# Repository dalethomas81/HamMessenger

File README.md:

> **⚠️ This repository is archived and no longer maintained.**  
> The code is left available for reference. No further updates, issues, or pull requests will be accepted.
> Please see [Meshtastic](https://meshtastic.org) or [Meshcore](https://meshcore.io) as superior alternatives. 

# HamMessenger # 

Hands on article about HamMessenger in IEEE Spectrum magazine [here](https://spectrum.ieee.org/ham-radio-text-hacking)  
Arduino blog post on HamMessenger [here](https://blog.arduino.cc/2021/07/27/send-text-messages-over-ham-radio-with-the-hammessenger/?queryID=undefined)  
Hackaday blog post on HamMessenger [here](https://hackaday.com/blog/?s=hammessenger)  

HamMessenger is a portable, battery powered device that runs on a microcontroller and interfaces with an inexpensive ham radio to send and receive text messages and provide position updates using the [APRS](http://www.aprs.org/doc/APRS101.PDF) protocol. Messages and position updates sent via HamMessenger can be viewed on sites such as [aprs.fi](https://aprs.fi). HamMessenger messages are NOT encrypted!  

HamMessenger is intended to be used by licensed ham radio operators. For more information you can check out the [ARRL](http://www.arrl.org/what-is-ham-radio) website.  

The goal of the HamMessenger project is to create a device that uses ham radio as a medium for sending and receiving text messages. HamMessenger exists also to promote amateur radio, electronics, and programming. The project is currently in a beta prototyping stage but does function quite well. 

At the core of the the project is the [MicroAPRS](https://github.com/markqvist/MicroAPRS) modem created by [markqvist](https://github.com/markqvist). The primary controller is an Arduino Mega 2560 with the MicroAPRS Modem running on an Arduino Pro Mini. HamMessenger includes GPS functionality supplied by a Neo-6M GPS radio. For peripherals, an M5Stack CardKB keyboard is used for input and an SSD1106 Oled display for output.  

I will add some videos and pictures of the device in action asap. Please feel free to contribute to the project. I am very busy outside of this project so any help is greatly appreciated :)  

<table>
  <tr>
    <td align="center">
      <br/>
      <sub>MacOS Log Screen</sub>
    </td>
    <td align="center">
      <br/>
      <sub>MacOS Map Screen</sub>
    </td>
  </tr>
</table>

<table>
  <tr>
    <td align="center">
      <br/>
      <sub>MacOS Message Screen</sub>
    </td>
    <td align="center">
      <br/>
      <sub>MacOS Commands Example</sub>
    </td>
  </tr>
</table>

<table>
  <tr>
    <td align="center">
      <br/>
      <sub>Full Enclosure</sub>
    </td>
    <td align="center">
      <br/>
      <sub>Component Layout</sub>
    </td>
    <td align="center">
      <br/>
      <sub>CAD Isometric</sub>
    </td>
  </tr>
</table>

## Operation ##

Full instructions on how to operate HamMessenger will go here. For now, just a couple notes :)  

HamMessenger will beacon your location and comment according to the 'Beacon' settings in `APRS` Settings.  
- `Beacon Distance` is the distance in miles that will trigger a beacon.  
- `Beacon Idle Time` is the time in milliseconds that the station must be in the same location after having moved from the last beacon location before a beacon will be sent.
- `Position Tolerance` under `GPS` settings is the +/- value that will trigger a location update.  

To send a direct message to a station, select `Messages` on the `HOME` screen and press `Enter` on the keyboard. This will open the `NEW MESSAGE` screen.  
- `Message Text` is the message that will be sent.  
- `Recipient Callsign` is the callsign of the station that will recieve the message. Example 'NOCALL-ID'  
- `Recipient SSID` is the ID of the station that will recieve the message. Example 'NOCALL-ID'  

Screen navigation information can be found [here](https://github.com/dalethomas81/HamMessenger/blob/master/Documentation/Operating%20Instructions/Screen%20Navigation.md).  

Radio setup instructions can be found [here](https://github.com/dalethomas81/HamMessenger/blob/master/Documentation/Operating%20Instructions/Radio%20Setup.md).

Serial interface information can be found [here](https://github.com/dalethomas81/HamMessenger/blob/master/Documentation/Operating%20Instructions/Serial%20Interface.md).

## TODO ##

hardware:
- improve enclosure design  

software:
- add ability to program the radio once connected for 'plug-n-play' experience (is this possible?)  
- add feature to be selective about message acknowledgments. currently any acknowlegment (from a second conversation) will reset the messaging sequencer.  

## Libraries ##

Here are links to the non-standard libraries that I am using for this project. All other libraries are standard and can be installed using the library manager built into the Arduino IDE.  
- https://github.com/wonho-maker/Adafruit_SH1106  
- https://github.com/mikalhart/TinyGPSPlus  
- https://github.com/adafruit/Adafruit-GFX-Library  
- https://github.com/Xander-Electronics/Base64  

## Compilation ##

The easiest way to compile HamMessenger is to use the Ardunio IDE. After all libraries are installed you can use the Verify button to compile or the Upload button to compile and write the binary to the main controller M1. 

The Arduino source code for HamMessenger can be found [here](/Source/HamMessenger).

The modem controller does not need to be compiled as the binary files are already made available [here](https://github.com/markqvist/MicroAPRS/tree/master/precompiled).  

You can use AVRDude to write the binary to the modem controller. Instructions on how to do that will be coming soon. In the meantime, if you already know how to install and use AVRDude then feel free to make use of the [batch](/Source/MicroAPRS%20Firmware%20Installer) file I created and an [FTDI](https://www.amazon.com/gp/product/B00DDF8TV6/ref=ox_sc_act_title_4?smid=A2SXV8GJXX3WPH&psc=1) serial cable to write to the modem.

## Parts ##

Find BOM information on parts [here](/Documentation/Parts/BOMs)  
Find Drawing information on parts [here](/Documentation/Parts/Drawings)  
Find Vendor information on parts [here](/Documentation/Parts/Vendors)  

### Part Specs ###

Arduino:  
https://gallery.autodesk.com/fusion360/projects/arduino-mega-2560-r3  

Keyboard:  
https://github.com/m5stack/M5-ProductExampleCodes/tree/master/Unit/CARDKB  

OLED Display:    
https://grabcad.com/library/0-96-oled-display-4-pin-1  
https://grabcad.com/library/ecran-oled-1-3-1

Modem:  
https://github.com/markqvist/MicroAPRS  
https://github.com/markqvist/MicroAPRS/blob/master/precompiled/microaprs-5v-ss-latest.hex  
https://github.com/markqvist/MicroAPRS/blob/master/documentation/Hardware%20Schematic.pdf  
https://unsigned.io/shop  
https://unsigned.io/product/micromodem-r23b  

GPS:    
https://grabcad.com/library/gps-module-ublox_neo6mv2-1  
https://grabcad.com/library/ecran-oled-1-3-1  

Grove Connector:  
https://grabcad.com/library/grove-connectors-stand-and-flat-male-plugs-1/details?folder_id=2820551  

Battery:  
Panasonic 18650 - don't have a link but you can get them on eBay or Amazon  

## Updates ##

### 31-MAY-2025: Major updates!

I have made some major updates to the board (RF filtering for the PTT), to the enclosure, and to the firmware (many improvements to the display including a dedicated "New Message" display). Additionally, I have created a companion GUI app that you can use to connect HamMessenger to your PC.  

I have ordered parts to begin building 3 new HamMessengers and will begin building them next week. The purpose is to create some instructional videos and documentation to help support anyone that wants to build one themselves. I also plan to donate these builds to my local Ham club.  

There is now a new [Build Instructions](/Documentation/Build%20Instructions/) folder that I will use to put the tutorial references and documentation.  

### 08-SEP-2021: Troubleshooting freezing

There is an issue where during transmit the unit will freeze or restart. I did some experimenting and found out that its the cable that connects to the radio. It is not shielded at all. I thought the small ferrites would be enough to combat this but obviously not. I did some experimenting and found that if I use larger ferrites and wrap them once that the issue goes away. [Here](/Media/Install/large-ferrites.jpeg/) is a picture of the installation. I will now look at sourcing a shielded cable for this application.

### 05-SEP-2021: First version of the enclosure

So I started learning 3D modeling so that I can create an enclosure for HamMessenger. Its been a bit of a learning curve but I'm getting the hang of it. I decided that for the first iteration I would go with an open unibody frame. I chose this style for the first version because it is easy and I'd like to have something working while I learn more about 3D modeling.

You can find the Fusion 360 archive file and the stl [here](/Documentation/CAD/Fusion-360/). It needs to be printed on its side like [this](/Media/Unibody-Frame-v1/cura.png/) to minimize the amount of support needed during printing. I used 0.2mm layers with 20% infill as well as 5% support infill. The print took about 6.5 hours.

A few pics:  
[Front](/Media/Unibody-Frame-v1/front.jpeg/)  
[Side](/Media/Unibody-Frame-v1/side.jpeg/)  
[Back](/Media/Unibody-Frame-v1/back.jpeg/)  

### 14-AUG-2021: Rev v1.1 has arrived and it works!

Ok, great news. Revision v1.1 of the HamMessenger board came in from PCBWay and they are great. I built 2 units and was able to encode and decode messages well. I will add some more information later but [here](/Media/Board-v1.1/) is a few pictures for now.

### 24-JUL-2021: Rev v1.1 is being fabbed!!

I was able to work through all of the issues with the first version. I placed an order with jlcpcb this time (osh park was great but too expensive). I ordered 20 boards this time and if they work well I will give some away.  

I'll update later with how I resolved the issues. For now, going to have a beer :)

### 22-JUL-2021: Put together some information on the board for your review.

[Here](/Media/Board-v1/analysis.md) is an in-depth analysis of the problems with version 1.0 of the board. Also, does any body know how to add correct shielding for the board? I am having issues with the Arduino locking up on transmit sometimes.

### 21-JUL-2021: Made revisons to the board resolving and improving the following:

1. add ground to SD card
2. add OE connection to line leveler
3. reverse I2C connections
4. change GPS I/O to correct serial
5. purchase correct GPS (added new link in BOM)
6. move SD card away from USB.
7. move keyboard grove to bottom of board and out of way
8. move 4 pin terminal for cable such that it is out of the way of larger OLED
9. ground plane improvements.  

still left to do:

1. board does not receive (soldering issues?)  
2. board some times locks up during transmit (ground plane issues?)  

### 20-JUL-2021: Bad news on the boards :( Lots of problems. I will begin immediately working on a revision. Here is a list of the issues:

1. SD Card missing ground
2. Line leveler missing OE connection.
3. I2C connections are reversed.
4. GPS is pointing to wrong serial ports (can fix with code but might as well make it right).
5. GPS pins do not match board. (worked around this by shifting pins)
6. Cannot not receive (don't know why at this point).
7. SD card hits Arduino USB. Will move it and the Grove connector to make room.
8. Arduino periodically locks up. Seemingly due to RF? Had this issue with prototype board but fixed it with ferrites.

### 18-JUL-2021: The printed circuit boards from OSH will be arriving tomorrow! I have added all of the parts needed to build HamMessenger [here](/Documentation/Parts/BOMs).

04-JUL-2021: Version 1 of the pcb for HamMessenger has be sent for fabrication. The estimated delivery date is the 22nd of July. In the meantime I will be ordering the components to populate the board. As I do that I will make sure to get the links for the components and add them to the BOM in the Eagle folder.

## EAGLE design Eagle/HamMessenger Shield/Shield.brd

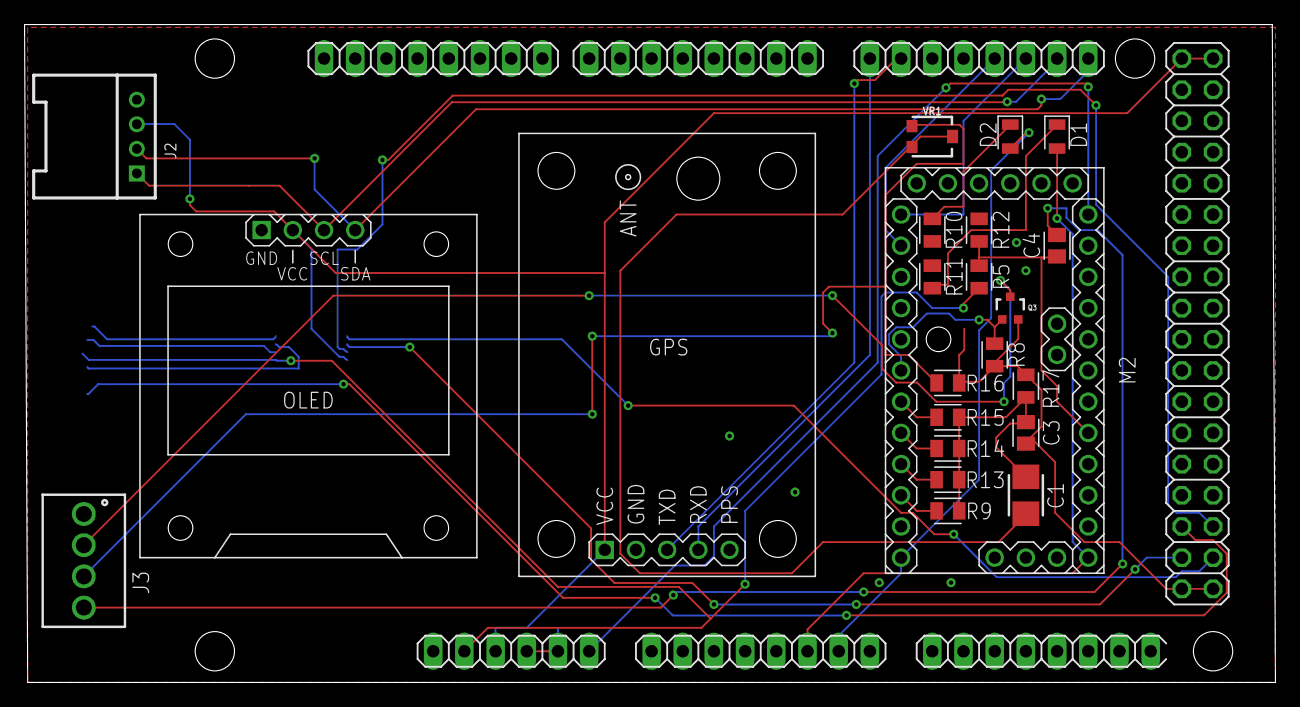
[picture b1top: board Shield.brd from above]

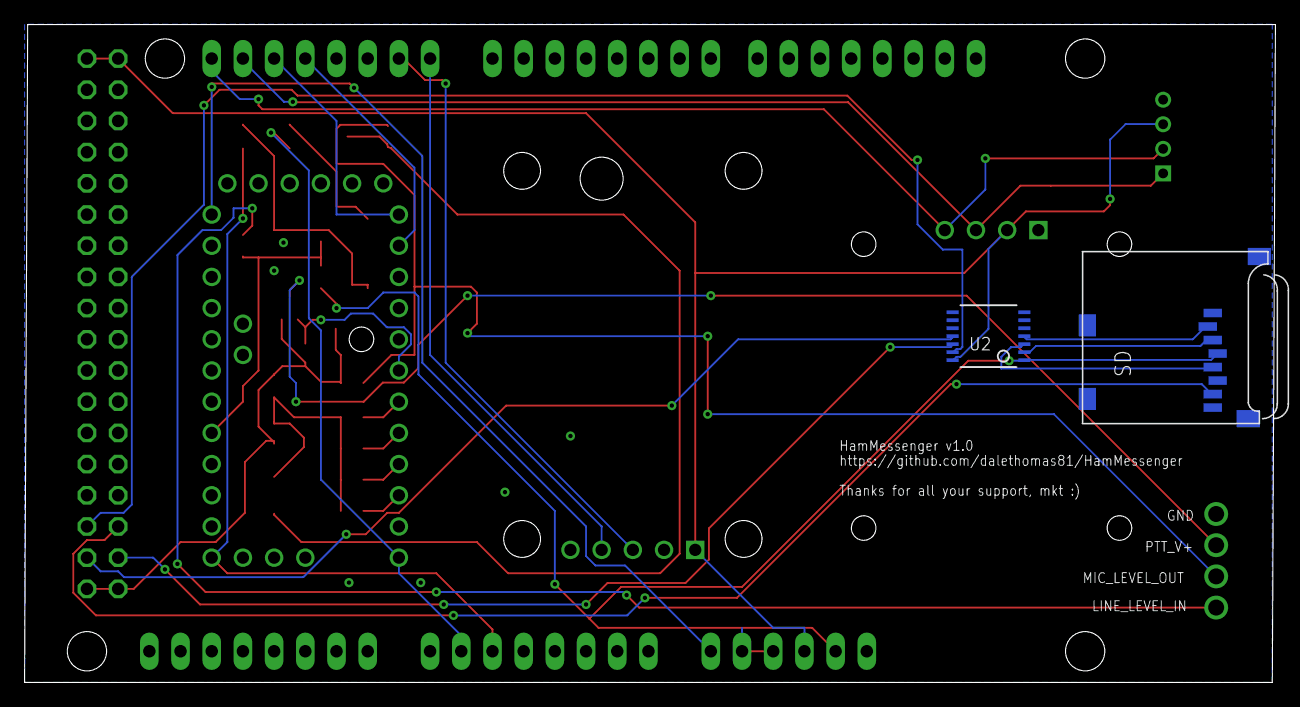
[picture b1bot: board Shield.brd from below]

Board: 2 copper layers, 101.9 x 53.6 mm, 26 parts (2 on the bottom side), 32 nets.

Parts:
C1: 4.7uf; CT3528
C3: 100nf; CAPC2012X110
C4: 1uf; CAPC2012X110
D1: LED_GREEN; LEDC2012X105N_RND-R
D2: LED_RED; LEDC2012X105N_RND-R
GPS: GPS-RECEIVER-NEO6M
J2: KEYBOARD GROVE; HW4-2.0-90D
J3: 691210910004
M1: MEGA_ARDUINO
M2: ARDUINO-PRO-MINI-3.3V; ARDUINO-PRO-MINI
OLED: DISPLAY-OLED-128X64-I2C
Q3: MOSFET-NCHANNEL2N7002PW; SOT323
R5, R12: 100k; RESC2012X65
R8: 10k; RESC2012X65
R9, R11, R16: 1k; RESC2012X65
R10: 270k; RESC2012X65
R13: 2k2; RESC2012X65
R14: 3k9; RESC2012X65
R15: 8k2; RESC2012X65
R17: 270; RESC2012X65
SD: MICROSD
U2: TSSOP14
VR1: 100k; TRIMPOT-SMD-3MM-CLOSED

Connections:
+3V3: M1.2, R5.2, SD.4, U2.1
+5V: GPS.1, J2.3, M1.3, M1.47, M1.48, OLED.2, U2.14
A0: C4.1, M2.J6.8, R5.1, R12.2
D3: M2.J7.7, Q3.1, R8.2
D4: M2.J7.6, R15.2
D5: M2.J7.5, R14.2
D6: M2.J7.4, R13.2
D7: M2.J7.3, R9.2
D9: D2.A, M1.13, M2.J7.1
D10: D1.A, M1.12, M2.J6.12
GND: C3.2, GPS.2, J2.4, J3.1, M1.4, M1.5, M1.45, M1.81, M1.82, M2.J6.2, M2.J7.9, OLED.1, Q3.2, R8.1, R10.1, R11.1, R12.1, R16.1, R17.1, SD.MT1, SD.MT2, U2.7
LINE_LEVEL_IN: C4.2, J3.4
LINE_LEVEL_OUT: C1.+, VR1.2, VR1.3
MIC_LEVEL_OUT: J3.3, R16.2, VR1.1
MISO: M1.77, SD.7
MOSI: M1.78, U2.13
unnamed: SD.3, U2.2
unnamed: C1.-, C3.1, R9.1, R13.1, R14.1, R15.1, R17.2
unnamed: D2.C, R10.2
unnamed: D1.C, R11.2
unnamed: SD.5, U2.3
unnamed: SD.2, U2.4
PTT_V+: J3.2, Q3.3
RX_GPS: GPS.3, M1.29
RX_MODEM: M1.25, M2.J7.12
SCK: M1.79, U2.12
SCL: J2.1, M1.24, OLED.3
SDA: J2.2, M1.23, OLED.4
SS: M1.80, U2.11
TX_GPS: GPS.4, M1.30
TX_MODEM: M1.26, M2.J7.11
VCC: M1.6, M2.J6.1, M2.J6.4

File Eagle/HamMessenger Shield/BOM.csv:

"Part";"Value";"Device";"Package";"Description";"CATEGORY";"COLOR";"URL";"PART-NUMBER";"PINS";"PITCH";"PROD_ID";"TYPE";"VALUE";"WORKING-VOLTAGE-UL";
"C1";"4.7uf";"CPOL-USCT3528";"CT3528";"POLARIZED CAPACITOR, American symbol";"Capacitor";;;"T591B475M035ATE200";;;;;;;
"C3";"100nf";"C_CHIP-0805(2012-METRIC)";"CAPC2012X110";"Capacitor - Generic";"Capacitor";;;"C0805C104J4RACTU";;;;;;;
"C4";"1uf";"C_CHIP-0805(2012-METRIC)";"CAPC2012X110";"Capacitor - Generic";"Capacitor";;;"C0805C105J4RECTU";;;;;;;
"D1";"Green";"CHIP-ROUND-R_0805";"LEDC2012X105N_RND-R";"LED - Generic";"LED";"RED";;"SM0805UGC";;;;"ROUND_TOP";"LED_RED";;
"D2";"Red";"CHIP-ROUND-R_0805";"LEDC2012X105N_RND-R";"LED - Generic";"LED";"RED";;"SM0805URC";;;;"ROUND_TOP";"LED_RED";;
"IC1";;"MEGAARDUINO_1";"MEGA_ARDUINO";"The Arduino Mega is a microcontroller board based on the ATmega2560";;;"https://www.amazon.com/ELEGOO-ATmega2560-ATMEGA16U2-Projects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";;;;;;;;
"J2";;"GROVE-CONNECTOR-DIP-90D(4P-2.0)";"HW4-2.0-90D";;;;"https://www.seeedstudio.com/Grove-Universal-4-pin-connector-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";"110990037";;;;;"4P-2.0-90D";;
"J3";;"691210910004";"691210910004";"WR-TBL Serie 2109 - 2.54 mm Horiz. Entry";;;"https://www.we-online.com/catalog/datasheet/691210910004.pdf";"282834-4";" 4 ";"2.54mm";;"Horizontal";;"150V (AC)";
"M1";;"ARDUINO-PRO-MINI-3.3V";"ARDUINO-PRO-MINI";"The Arduino Mega is a microcontroller board based on the ATmega328P";;;"https://www.amazon.com/HiLetgo-Atmega328P-Replace-ATmega128-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";;;;;;;;
"Q3";;"MOSFET-NCHANNEL2N7002PW";"SOT323";"Common NMOSFET Parts";;;;;;;"TRANS-11151";;;;
"R5";"100k";"R_CHIP-0805(2012-METRIC)";"RESC2012X65";"Resistor Fixed - Generic";"Resistor";;;;;;;;;;
"R8";"10k";"R_CHIP-0805(2012-METRIC)";"RESC2012X65";"Resistor Fixed - Generic";"Resistor";;;;;;;;;;
"R9";"1k";"R_CHIP-0805(2012-METRIC)";"RESC2012X65";"Resistor Fixed - Generic";"Resistor";;;;;;;;;;
"R10";"270k";"R_CHIP-0805(2012-METRIC)";"RESC2012X65";"Resistor Fixed - Generic";"Resistor";;;;;;;;;;
"R11";"1k";"R_CHIP-0805(2012-METRIC)";"RESC2012X65";"Resistor Fixed - Generic";"Resistor";;;;;;;;;;
"R12";"100k";"R_CHIP-0805(2012-METRIC)";"RESC2012X65";"Resistor Fixed - Generic";"Resistor";;;;;;;;;;
"R13";"2k2";"R_CHIP-0805(2012-METRIC)";"RESC2012X65";"Resistor Fixed - Generic";"Resistor";;;;;;;;;;
"R14";"3k9";"R_CHIP-0805(2012-METRIC)";"RESC2012X65";"Resistor Fixed - Generic";"Resistor";;;;;;;;;;
"R15";"8k2";"R_CHIP-0805(2012-METRIC)";"RESC2012X65";"Resistor Fixed - Generic";"Resistor";;;;;;;;;;
"R16";"1k";"R_CHIP-0805(2012-METRIC)";"RESC2012X65";"Resistor Fixed - Generic";"Resistor";;;;;;;;;;
"R17";"270";"R_CHIP-0805(2012-METRIC)";"RESC2012X65";"Resistor Fixed - Generic";"Resistor";;;;;;;;;;
"GPS";;"GPS-RECEIVER-NEO6M";"GPS-RECEIVER-NEO6M";"GPS Receiver Module based on NEO-6 device";;;;;;;;;;;
"OLED";;"DISPLAY-OLED-128X64-I2C";"DISPLAY-OLED-128X64-I2C";"128x64 Dot Matrix OLED Module based on SSD1306 chip";;;;;;;;;;;
"SD";;"MICROSD";"MICROSD";"Micro-SD / Transflash card holder with SPI pinout";;;;;;;;;;;
"U2";;"TXB0104PWR";"TSSOP14";"4-Bit Bi-Directional Level Shifter";;;;;;;;;;;
"VR1";"100k";"TRIMPOT-SMD-3MM-CLOSED-1/8W-20%";"TRIMPOT-SMD-3MM-CLOSED";"Trimming Potentiometer (Trimpot)";;;;;;;"RES-09285";;"10k";;

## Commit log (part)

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2021-06-26 init
2021-06-26 add media
2021-06-27 add serial commands table
2021-06-27 update readme. add print and save to serial
2021-06-27 Convert settings array references to use macros
2021-06-27 Improve readme serial commands
2021-06-27 add modem command to printout
2021-06-27 improve serial commands in readme
2021-06-27 Add raw packet info
2021-06-27 clarify what HamMessenger is
2021-06-27 add uint edit to aprs settings
2021-06-27 esc button cancels edit. enter button confirms.
2021-06-27 use temp variable for strings
2021-06-27 add remaining settings to temp variables
2021-06-27 remove reference to buttons
2021-06-27 add #defines for keyboard keys
2021-06-27 add macros for keyboard keys
2021-06-27 add edit capability to settings_gps
2021-06-27 add edit capablities to settings_display
2021-06-27 optimize settings screen
2021-06-27 fix issue where float doesnt copy to temp var
2021-06-28 fix issue where float val does not negate
2021-06-28 general code cleanup. update readme.
2021-06-28 refactor temp var handling into functions
2021-06-28 refactor printing value stored in mem to function
2021-06-28 general refactoring
2021-06-29 Begin work on PCB. Add schematic (WIP)
2021-06-30 Continue work on PCB. Update schematic.
2021-07-01 Fix settings arent accepted via command prompt
2021-07-01 Add quick way to send messages. Update readme.
2021-07-01 Fix issue with dynamic number of items in settings
2021-07-01 added sequencer for sending messages
2021-07-02 init test writing and reading sd card
2021-07-02 remove unneeded reference to SD library
2021-07-02 general code clean up and variable optimizing
2021-07-02 code clean up
2021-07-02 General refactoring. Update readme.
2021-07-02 add feature to retry messages if not acknowledged
2021-07-03 add retry count and interval to settings.
2021-07-03 add display timeout - dim then turn off
2021-07-03 key press only register when screen awake
2021-07-03 variable names cleanup
2021-07-03 fix issue with gps tolerance
2021-07-03 update readme and settings names.
2021-07-03 add references
2021-07-03 add dxf for arduino mega 2560
2021-07-03 add notes. start ui documentation.
2021-07-03 improve message and feed scrolling.
2021-07-04 Add screenshots. Continue work on UI map.
2021-07-04 test relative path image
2021-07-04 check
2021-07-04 Update UI
2021-07-04 add screenshots
2021-07-04 Formatting
2021-07-04 Net re-routing
2021-07-04 PCB Updates
2021-07-04 Add ground plane
2021-07-04 add SD card. rerouting.
2021-07-05 Update readme. Add isometic view.
2021-07-05 Update readme. Relative photos.
2021-07-05 add grove connector
2021-07-05 Add text to silkscreen
2021-07-05 Change pins grove keyboard connector.
2021-07-05 Last minute tweeks before sending to fab.
2021-07-05 Serial commands. Formattings.
2021-07-05 Screen navigation
2021-07-05 BOM updates
2021-07-05 Add cardkb
2021-07-05 updated schematic and BOM
2021-07-10 add define to set which display is used
2021-07-10 remove references to SSD1306 oled library
2021-07-10 test 1
2021-07-11 Add copywrite info
2021-07-11 add gitignore
2021-07-11 Add write raw to SD. Add date time to structs
2021-07-11 read and write raw and messages. print to terminal
2021-07-11 Fix link issues
2021-07-11 Add information on parts and libraries.
2021-07-11 readme fix
2021-07-11 hotfix
2021-07-11 add sd delete. update terminal commands.
2021-07-11 reduce dynamic memory usage from commands
2021-07-11 update on libraries
2021-07-11 ninja edit
2021-07-12 add test
2021-07-12 open 2 files at once and keep open
2021-07-12 getRawDataRecord
2021-07-12 read raw data from SD on Live Feed screen
2021-07-12 Update Live Feed
2021-07-12 Live Feed updates
2021-07-13 add code to get msg record
2021-07-13 Build success - add getMsgDataRecord
2021-07-13 clean up
2021-07-13 bug in messages
2021-07-14 code clean up. improve record count on displays
2021-07-15 fix issue where SD file buffer overflows
2021-07-17 display improvements and code cleanup
2021-07-18 Move source files
2021-07-18 Add instructions for radio setup
2021-07-18 mover serial commands to dedicated page
2021-07-18 Rearrange folders
2021-07-18 Move source code
2021-07-18 Radio usage
2021-07-19 Update Mouser BOM for 1 HamMessenger
2021-07-19 make BOMs more clear. Add BOM info.
2021-07-19 Add clarity to readme. add shared board link
2021-07-19 add clarity
2021-07-21 Board updates
2021-07-22 Board fixes / improvements
2021-07-22 add command for mac to use avrdude.
2021-07-23 board analysis
2021-07-24 final touch before fab
2021-07-24 gerber files and jlcpcb cam
2021-07-28 convert position tolerance to degrees
2021-07-28 add terminal commands for GPS
2021-07-28 rearrange methods. add check for '-' in float data
2021-07-28 add clarification about APRS table
2021-07-28 show Standard/Alternate for APRS table
2021-08-15 add infor on v1.1
2021-09-05 add unibody frame files
2021-09-05 update readme on unibody frame
2021-09-05 readme
2021-09-08 update arduino extension settings vscode
2021-09-09 update ferrite application
2023-01-29 remove typo. update arduino config.
2025-05-04 hello world gui
2025-05-04 git ignore. send new line.
2025-05-04 print raw messages
2025-05-04 firmware
2025-05-05 log filtering
2025-05-05 clear message string
2025-05-05 enter to send
2025-05-05 gui screenshot
2025-05-06 add breather for read_serial
2025-05-06 add map tab showing locations
2025-05-06 marker data. mic-E testing.
2025-05-06 testing aprspy
2025-05-06 aprspy testing
2025-05-07 mic-e decode, message threading
2025-05-07 requirements, installation, gitignore, executable
2025-05-07 wash gitignore
2025-05-07 move marker instead of duplicate
2025-05-07 add emoji to marker
2025-05-08 parse SD data to map
2025-05-08 base64 encode SD card data
2025-05-08 Raw SD card print non-blocking
2025-05-08 clean up serial output
2025-05-09 disable pan to marker
2025-05-09 add new message display
2025-05-09 merge
2025-05-10 display organization
2025-05-11 move CAD into source folder
2025-05-11 messages bug
2025-05-11 front cover
2025-05-11 display visibility
2025-05-11 display code refactoring
2025-05-11 add enclosure front cover. clean old files.
2025-05-11 trigger message handling
2025-05-11 hotfix null terminate raw modem
2025-05-12 back cover. front cover gps.
2025-05-13 GPS display improvements
2025-05-13 add smart beaconing
2025-05-14 gitignore
2025-05-14 enclosure. gps logic.
2025-05-15 smart beacon. hotfix parameters. debug screen.
2025-05-15 debug screen
2025-05-15 debug
2025-05-16 mac gui tweaks
2025-05-17 update PCB with RC filter for RF mitigation
2025-05-17 update BOM
2025-05-18 documentation
2025-05-18 New views
2025-05-26 Update CAD view
2025-05-26 add nightly workflow
2025-05-26 update nightly build
2025-05-26 update nightly
2025-05-26 update workflow
2025-05-26 update workflow and requirments
2025-05-26 add scrollable input fields
2025-05-27 - fix issue where raw modem output is null terminated too short. - increased the SSID size from 1 character to 2 characters. - add ability to scroll text in and out of the window using left and right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
2025-05-28 add input data validation for settings
2025-05-28 add string 2 for symbol table
2025-05-28 define magic numbers
2025-05-28 automatically go to end of input strings longer than display.
2025-05-28 refactor display builder. add closing cursor.
2025-05-29 memory optimizations
2025-05-30 fix gui theme for macos
2025-05-30 remove gui dark theme for windows
2025-05-30 clean up gui
2025-05-30 add master workflow
2025-06-01 gui messages
2025-06-01 [Qt.py] add pins to map
2025-06-01 [Qt] updates
2025-06-01 auto-scroll
2025-06-01 build action
2025-06-01 build actions
2025-06-02 gui layout
2025-06-02 layout helper
2025-06-03 add info to pin popup
2025-06-03 add messages
2025-06-03 [GUI] add message box
2025-06-03 refactor def
2025-06-04 readme screenshots
2025-06-04 readme relative paths
2025-06-04 microaprs documentation
2025-06-04 development workflow
2025-06-04 Add github token to workflow
2025-06-04 ncipollo workflow
2025-06-04 create release workflow
2025-06-04 update workflows
2025-06-04 release badge
2025-06-05 Update issue templates
2025-06-07 resolve issue with terminal SSID command
2025-06-07 add file size warning when writing
2025-06-08 generate shield v1.2 schematics
2025-06-08 tighten up front cover. remove material new cable
2025-06-08 add dark mode monitoring for MacOS
2025-06-08 [GUI] change colors based on dark mode
2025-06-08 add check for macos before using pyobjc
2025-06-08 [GUI] add windows dark mode monitoring
2025-06-09 [Terminal] resolve issues with string names and size
2025-06-12 resolve issue with default settings
2025-06-13 update radio setup
2025-06-13 add sleep in serial connection thread
2025-11-25 export pick and place positions
2026-03-14 create wiki docs

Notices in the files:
parts and their libraries:
diy-modules: Released under the Creative Commons Attribution 4.0 International License: http://creativecommons.org/licenses/by/4.0
SparkFun-Resistors: Licensing: Creative Commons ShareAlike 4.0 International - https://creativecommons.org/licenses/by-sa/4.0
